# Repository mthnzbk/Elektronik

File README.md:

# elektronik
 Arduino ve diğer elektronik kartlar ile yapılmış kodlar ve devreler

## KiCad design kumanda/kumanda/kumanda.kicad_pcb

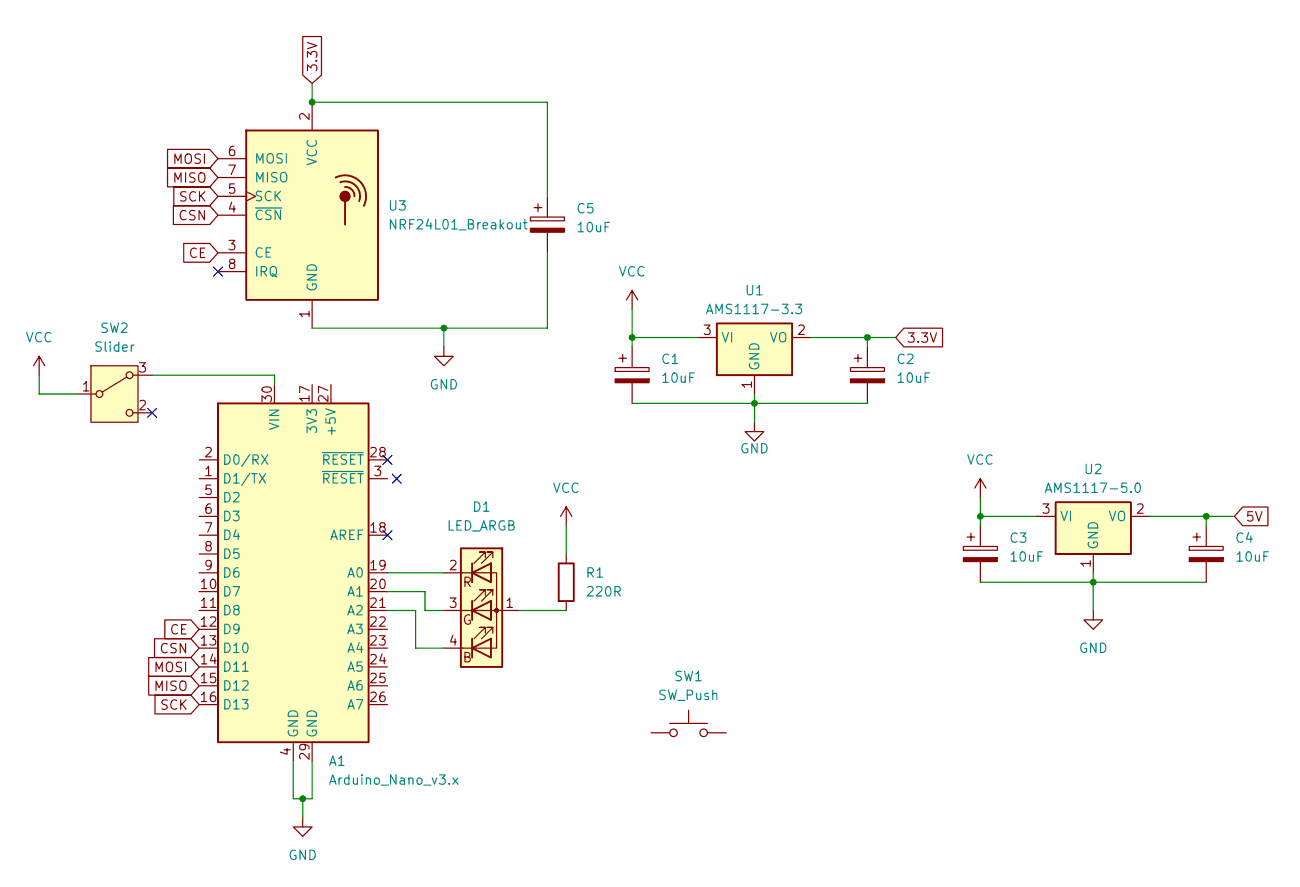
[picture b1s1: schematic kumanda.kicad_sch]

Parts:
A1: Arduino_Nano_v3.x; Arduino_Nano_WithMountingHoles
C1, C2, C3, C4, C5: 10uF; CP_EIA-3216-10_Kemet-I
D1: LED_ARGB; LED_D5.0mm-4_RGB
R1: 220R; R_2010_5025Metric
SW1: SW_Push; SW_PUSH-12mm
SW2: Slider; SW_Slide-03_Wuerth-WS-SLTV_10x2.5x6.4_P2.54mm
U1: AMS1117-3.3; SOT-223-3_TabPin2
U2: AMS1117-5.0; SOT-223-3_TabPin2
U3: NRF24L01_Breakout; nRF24L01_Breakout

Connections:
3.3V: C2.1, C5.1, U1.2 (VO), U3.2 (VCC)
5V: C4.1, U2.2 (VO)
CE: A1.12 (D9), U3.3 (CE)
CSN: A1.13 (D10), U3.4 (~CSN)
GND: A1.4 (GND), A1.29 (GND), C1.2, C2.2, C3.2, C4.2, C5.2, U1.1 (GND), U2.1 (GND), U3.1 (GND)
MISO: A1.15 (D12), U3.7 (MISO)
MOSI: A1.14 (D11), U3.6 (MOSI)
unnamed: A1.19 (A0), D1.2 (RK)
unnamed: A1.20 (A1), D1.3 (GK)
unnamed: A1.21 (A2), D1.4 (BK)
unnamed: A1.30 (VIN), SW2.3 (A)
unnamed: D1.1 (A), R1.2
SCK: A1.16 (D13), U3.5 (SCK)
VCC: C1.1, C3.1, R1.1, SW2.1 (B), U1.3 (VI), U2.3 (VI)

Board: 2 copper layers, 13 parts (0 on the bottom side), 14 nets, no tracks yet.

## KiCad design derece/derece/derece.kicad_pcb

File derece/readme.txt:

Devre şemasına buradan ulaşabilirsiniz.

 https://oshwlab.com/mthnzbk/temp

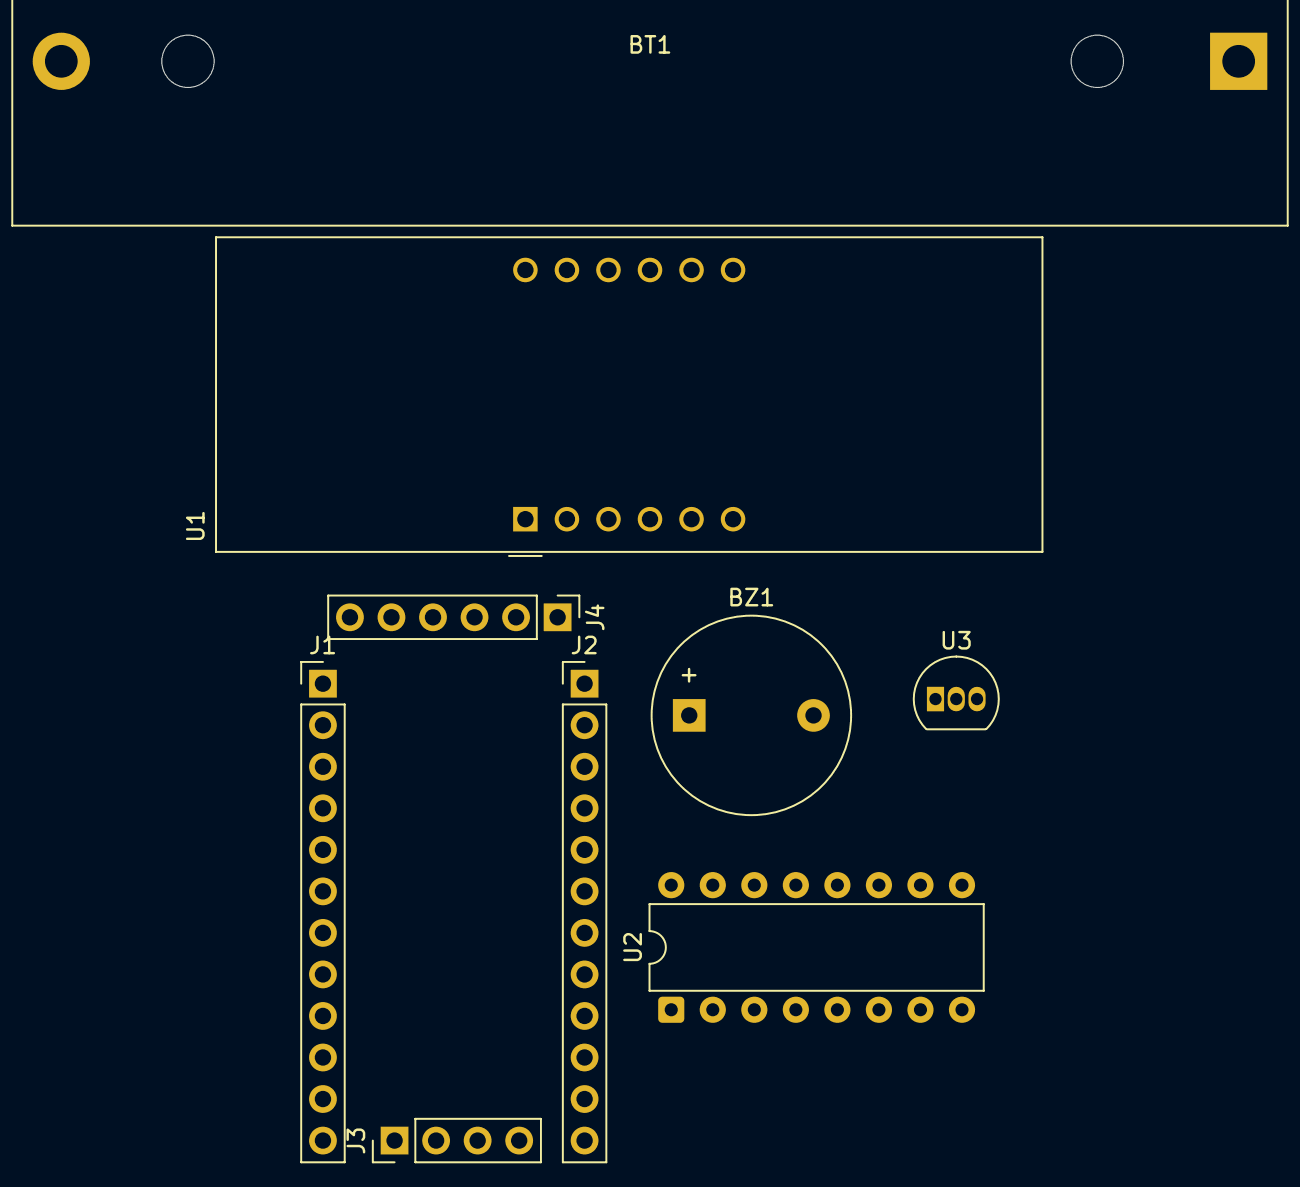
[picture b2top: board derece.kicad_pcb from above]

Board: 2 copper layers, 9 parts (0 on the bottom side), 6 nets, no tracks yet.

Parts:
BT1: Battery; BatteryHolder_MPD_BH-18650-PC2
BZ1: Buzzer; Buzzer_12x9.5RM7.6
J1, J2: PinHeader_1x12_P2.54mm_Vertical
J3: PinHeader_1x04_P2.54mm_Vertical
J4: PinHeader_1x06_P2.54mm_Vertical
U1: CA56-12SURKWA; CA56-12CGKWA
U2: 74HC595; DIP-16_W7.62mm
U3: LM35-LP; TO-92_Inline

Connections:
A0: J2.8, U3.2 (V_{OUT})
GND: BT1.2 (-), J1.4, J2.2, J4.5, J4.6, U2.8 (GND), U3.3 (GND)
RST: J1.3, J2.3
RX: J1.2, J4.3
TX: J1.1, J4.2
VCC: BT1.1 (+), J2.4, J4.4, U2.16 (VCC), U3.1 (+V_{S})

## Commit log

2025-03-31 devre şeması
2025-03-31 kablosuz veri ile lamba açan anahtar kodu ve fritzing şeması
2025-03-31 kablosuz olarak gelen veri ile röleyi devreye alıp lambayı yakan kod ve fritzing şeması.
2025-04-15 rgb led yumuşak geçişli
2025-05-05 bluetoothlu vibrasyon
